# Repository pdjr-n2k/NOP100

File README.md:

# NOP100

The **NOP100** project implements a generic
[NMEA 2000](https://en.wikipedia.org/wiki/NMEA_2000)
module with on-board support for
[MikroBUS](https://www.mikroe.com/mikrobus)
and
[OneWire]()
devices.

Twin MikroBUS sockets allow specialisation of function by the addition of
[Click](https://www.mikroe.com/click)
expansion cards and appropriate software extensions.

[**NOP100** hardware](./hardware/README.md)
is based on the Teensy 4.0 micro-controller supported by a CAN
transceiver, parasitic power supply and a user configuration
interface.

[**NOP100** firmware](./firmware/README.md)
manages NMEA 2000 connectivity, user interaction and module
configuration and is easily extended by the addition of firmware
dedicated to interfacing any installed MikroBus and OneWire devices.

## Project organisation

```
NOP100/
  + firmware/            # NOP100 firmware...
    + modules/           # Folders for module specialisations
      + NOP100-SIM/        # Specialisation defining an NMEA switch input module
        + defines.h
        + definitions.h
        + includes.h
        + loop.h
        + setup.h
      + another module specialisation/
      + .../
    + NOP100.cpp         # NOP100 main application 
    + README.md
    + defines.h          # Symbolic link to a module specialisation
    + definitions.h      #   "       "
    + includes.h         #   "       "
    + loop.h             #   "       "
    + setup.h            #   "       "
  + hardware/            # NOP100 hardware...
    + gerber/            # Gerber files for PCB fabrication
    + kicad/             # Kicad design for the NOP100 motherboard
    + README.md
```

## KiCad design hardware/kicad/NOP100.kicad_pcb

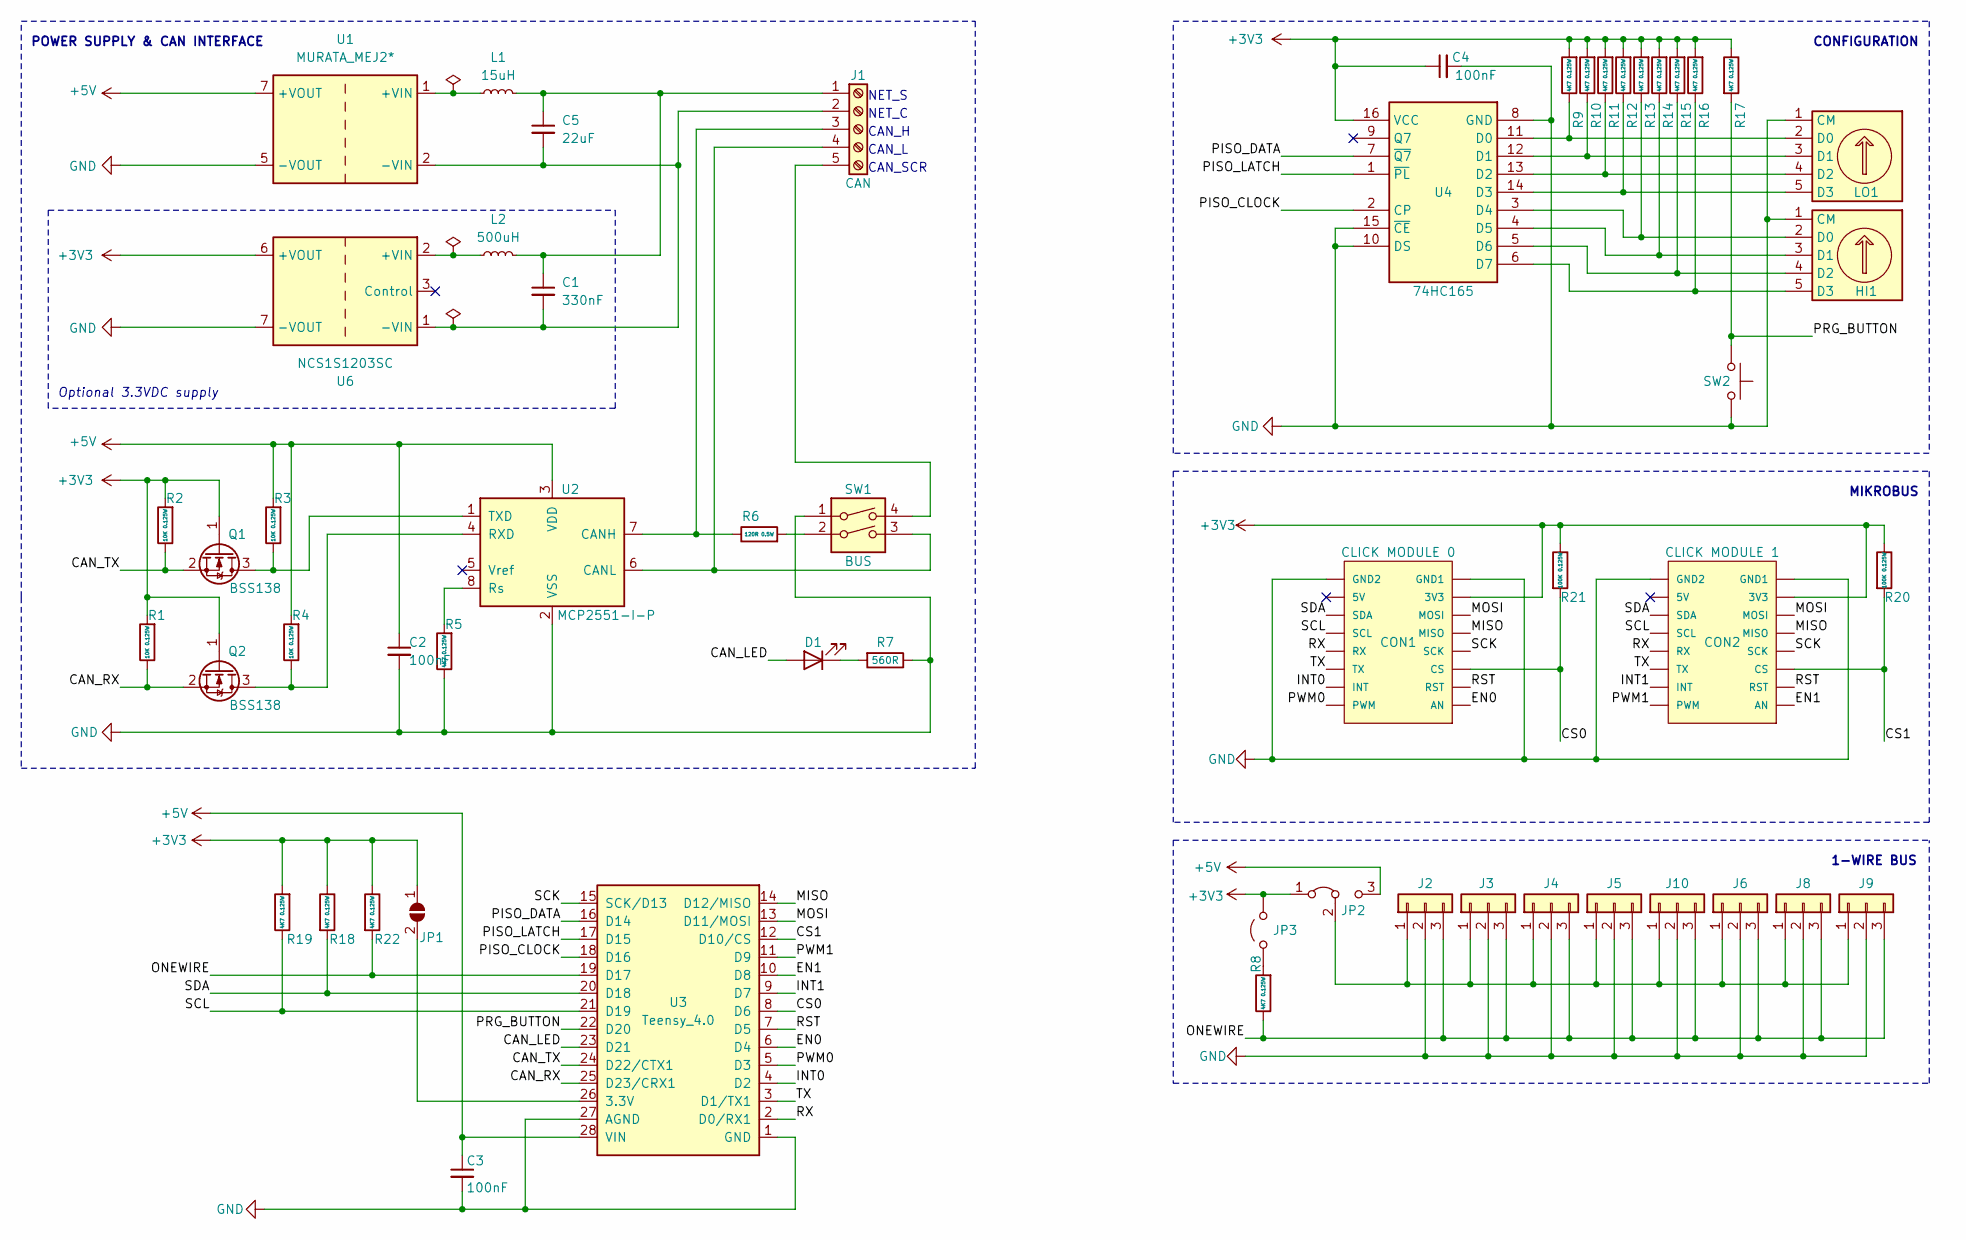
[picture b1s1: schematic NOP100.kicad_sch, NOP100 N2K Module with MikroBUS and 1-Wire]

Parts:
C1: 330nF; R_1210_3225Metric
C2, C3, C4: 100nF; R_0805_2012Metric
C5: 22uF; R_1210_3225Metric
CON1: CLICK MODULE 0; MIKROBUS_HOST_CONN
CON2: CLICK MODULE 1; MIKROBUS_HOST_CONN
D1: LED; R_0805_2012Metric
HI1: SW_Coded; Nidec_Copal_SH-7010C
J1: CAN; PinHeader_1x05_P2.54mm_Vertical
J2, J3, J4, J5, J6, J8, J9, J10: Conn_01x03; RS_8971054
JP1: SolderJumper_2_Open; SolderJumper-2_P1.3mm_Bridged_Pad1.0x1.5mm
JP2: Jumper_3_Bridged12; PinHeader_1x03_P1.27mm_Vertical
JP3: Jumper_2_Open; PinHeader_1x02_P1.27mm_Vertical
L1: 15uH; L_Bourns_SRN6045TA
L2: 500uH; L_Bourns_SRN6045TA
LO1: SW_Coded; Nidec_Copal_SH-7010C
Q1, Q2: BSS138; SOT-23
R1, R2, R3, R4: 10K 0.125W; R_0805_2012Metric
R5, R8, R9, R10, R11, R12, R13, R14, R15, R16, R17, R18, R19, R22: 4K7 0.125W; R_0805_2012Metric
R6: 120R 0.5W; R_1206_3216Metric
R7: 560R; R_0805_2012Metric
R20, R21: 100K 0.125W; R_0805_2012Metric
SW1: BUS; DIP-4_W7.62mm_LongPads
SW2: SW_Push; SW_SPST_PTS810
U1: MURATA_MEJ2*; Murata-MEJ2*
U2: MCP2551-I-P; SOIC-8_3.9x4.9mm_P1.27mm
U3: Teensy_4.0; DIP-28_W15.24mm_Socket
U4: 74HC165; SOIC-16_3.9x9.9mm_P1.27mm
U6: NCS1S1203SC; Converter_DCDC_Murata_NCS1SxxxxSC_THT

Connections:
+3V3: C4.1, CON1.P7 (3V3), CON2.P7 (3V3), JP1.1 (A), JP2.1 (A), JP3.2 (B), Q1.1 (G), Q2.1 (G), R1.2, R2.2, R9.2, R10.2, R11.2, R12.2, R13.2, R14.2, R15.2, R16.2, R17.1, R18.1, R19.2, R20.1, R21.1, R22.1, U4.16 (VCC), U6.6 (+VOUT)
+5V: C2.1, C3.1, JP2.3 (B), R3.2, R4.2, U1.7 (+VOUT), U2.3 (VDD), U3.28 (VIN)
/CAN_LED: D1.2 (A), U3.23 (D21)
/CAN_RX: Q2.2 (S), R1.1, U3.25 (D23/CRX1)
/CAN_TX: Q1.2 (S), R2.1, U3.24 (D22/CTX1)
/CS0: CON1.P3 (CS), R21.2, U3.8 (D6)
/CS1: CON2.P3 (CS), R20.2, U3.12 (D10/CS)
/EN0: CON1.P1 (AN), U3.6 (D4)
/EN1: CON2.P1 (AN), U3.10 (D8)
/INT0: CON1.P15 (INT), U3.4 (D2)
/INT1: CON2.P15 (INT), U3.9 (D7)
/MISO: CON1.P5 (MISO), CON2.P5 (MISO), U3.14 (D12/MISO)
/MOSI: CON1.P6 (MOSI), CON2.P6 (MOSI), U3.13 (D11/MOSI)
/ONEWIRE: J2.3, J3.3, J4.3, J5.3, J6.3, J8.3, J9.3, J10.3, R8.1, R22.2, U3.19 (D17)
/PISO_CLOCK: U3.18 (D16), U4.2 (CP)
/PISO_DATA: U3.16 (D14), U4.7 (~Q7)
/PISO_LATCH: U3.17 (D15), U4.1 (~PL)
/PRG_BUTTON: R17.2, SW2.1, U3.22 (D20)
/PWM0: CON1.P16 (PWM), U3.5 (D3)
/PWM1: CON2.P16 (PWM), U3.11 (D9)
/RST: CON1.P2 (RST), CON2.P2 (RST), U3.7 (D5)
/RX: CON1.P13 (RX), CON2.P13 (RX), U3.2 (D0/RX1)
/SCK: CON1.P4 (SCK), CON2.P4 (SCK), U3.15 (SCK/D13)
/SCL: CON1.P12 (SCL), CON2.P12 (SCL), R19.1, U3.21 (D19)
/SDA: CON1.P11 (SDA), CON2.P11 (SDA), R18.2, U3.20 (D18)
/TX: CON1.P14 (TX), CON2.P14 (TX), U3.3 (D1/TX1)
GND: C2.2, C3.2, C4.2, CON1.P8 (GND1), CON1.P9 (GND2), CON2.P8 (GND1), CON2.P9 (GND2), HI1.1 (CM), J2.2, J3.2, J4.2, J5.2, J6.2, J8.2, J9.2, J10.2, LO1.1 (CM), R5.1, R7.1, SW1.1, SW2.2, U1.5 (-VOUT), U2.2 (VSS), U3.1 (GND), U3.27 (AGND), U4.8 (GND), U4.10 (DS), U4.15 (~CE), U6.7 (-VOUT)
unnamed: D1.1 (K), R7.2
unnamed: HI1.2 (D0), R13.1, U4.3 (D4)
unnamed: HI1.3 (D1), R14.1, U4.4 (D5)
unnamed: HI1.4 (D2), R15.1, U4.5 (D6)
unnamed: HI1.5 (D3), R16.1, U4.6 (D7)
unnamed: C1.1, C5.1, J1.1, L1.2, L2.2
unnamed: C1.2, C5.2, J1.2, U1.2 (-VIN), U6.1 (-VIN)
unnamed: J1.3, R6.1, U2.7 (CANH)
unnamed: J1.4, SW1.3, U2.6 (CANL)
unnamed: J1.5, SW1.4
unnamed: J2.1, J3.1, J4.1, J5.1, J6.1, J8.1, J9.1, J10.1, JP2.2 (C)
unnamed: JP1.2 (B), U3.26 (3.3V)
unnamed: JP3.1 (A), R8.2
unnamed: LO1.2 (D0), R9.1, U4.11 (D0)
unnamed: LO1.3 (D1), R10.1, U4.12 (D1)
unnamed: LO1.4 (D2), R11.1, U4.13 (D2)
unnamed: LO1.5 (D3), R12.1, U4.14 (D3)
unnamed: Q1.3 (D), R3.1, U2.1 (TXD)
unnamed: Q2.3 (D), R4.1, U2.4 (RXD)
unnamed: R6.2, SW1.2
unnamed: L1.1, U1.1 (+VIN)
unnamed: R5.2, U2.8 (Rs)
unnamed: L2.1, U6.2 (+VIN)

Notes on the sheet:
CONFIGURATION
1-WIRE BUS
MIKROBUS
CAN_H
POWER SUPPLY & CAN INTERFACE
CAN_L
CAN_SCR
NET_C
NET_S
Optional 3.3VDC supply

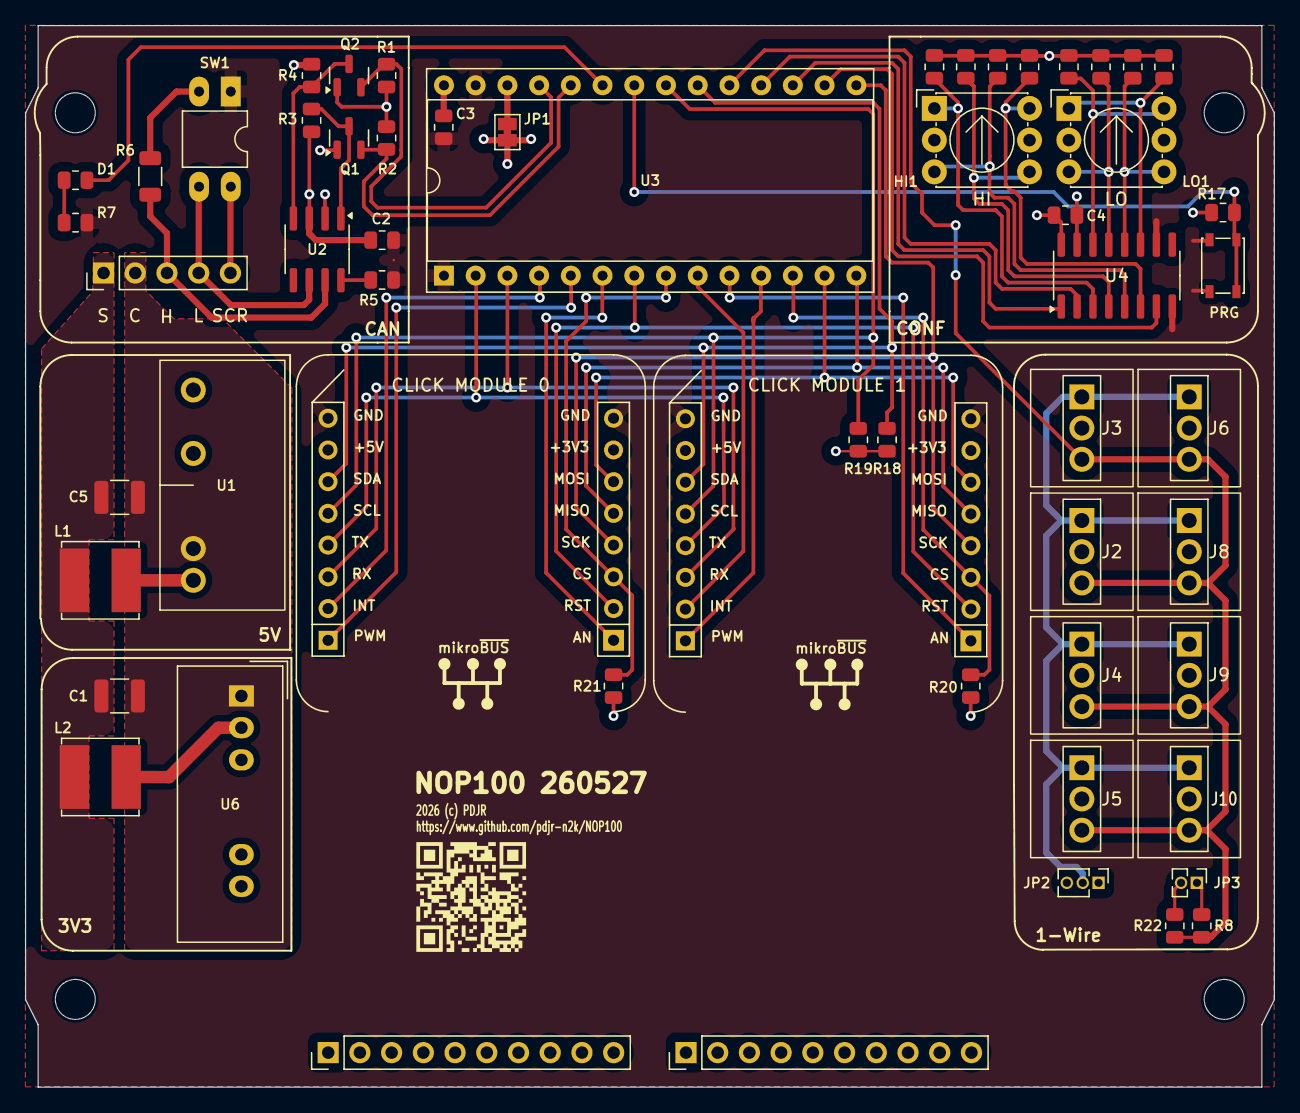
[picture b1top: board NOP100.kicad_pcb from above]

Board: 4 copper layers, 100.0 x 85.0 mm, 55 parts (0 on the bottom side), 50 nets.

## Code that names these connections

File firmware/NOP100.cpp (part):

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#define GPIO_SPI_MOSI GPIO_D11
#define GPIO_SPI_MISO GPIO_D12
#define GPIO_SPI_SCK GPIO_D13
#define GPIO_PISO_DATA GPIO_D14
#define GPIO_PISO_LATCH GPIO_D15
#define GPIO_PISO_CLOCK GPIO_D16
#define GPIO_ONE_WIRE GPIO_D17
#define GPIO_I2C_SDA GPIO_D18
#define GPIO_I2C_SCL GPIO_D19
#define GPIO_BUTTON_PRG GPIO_D20
#define GPIO_LED_CAN GPIO_D21
#define GPIO_CAN_TX GPIO_D22
#define GPIO_CAN_RX GPIO_D23

/**********************************************************************
 * @brief NMEA2000 device information.
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 * @brief Interface to the IC74HC165 PISO IC that connects the eight 
 *        DIL switch parallel inputs.
 */
IC74HC165 CodeSwitchPISO (GPIO_PISO_CLOCK, GPIO_PISO_DATA, GPIO_PISO_LATCH);

/**
 * @brief tLedManager objects for operating the CAN and PRG LEDs.
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
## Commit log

2026-05-25 Tweaks galore
2026-05-25 Tweaks

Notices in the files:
firmware/NOP100.cpp:
@copyright Copyright (c) 2023
